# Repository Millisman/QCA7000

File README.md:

# QCA7000
QCA7000 PLC Board
1. TODO Not tested

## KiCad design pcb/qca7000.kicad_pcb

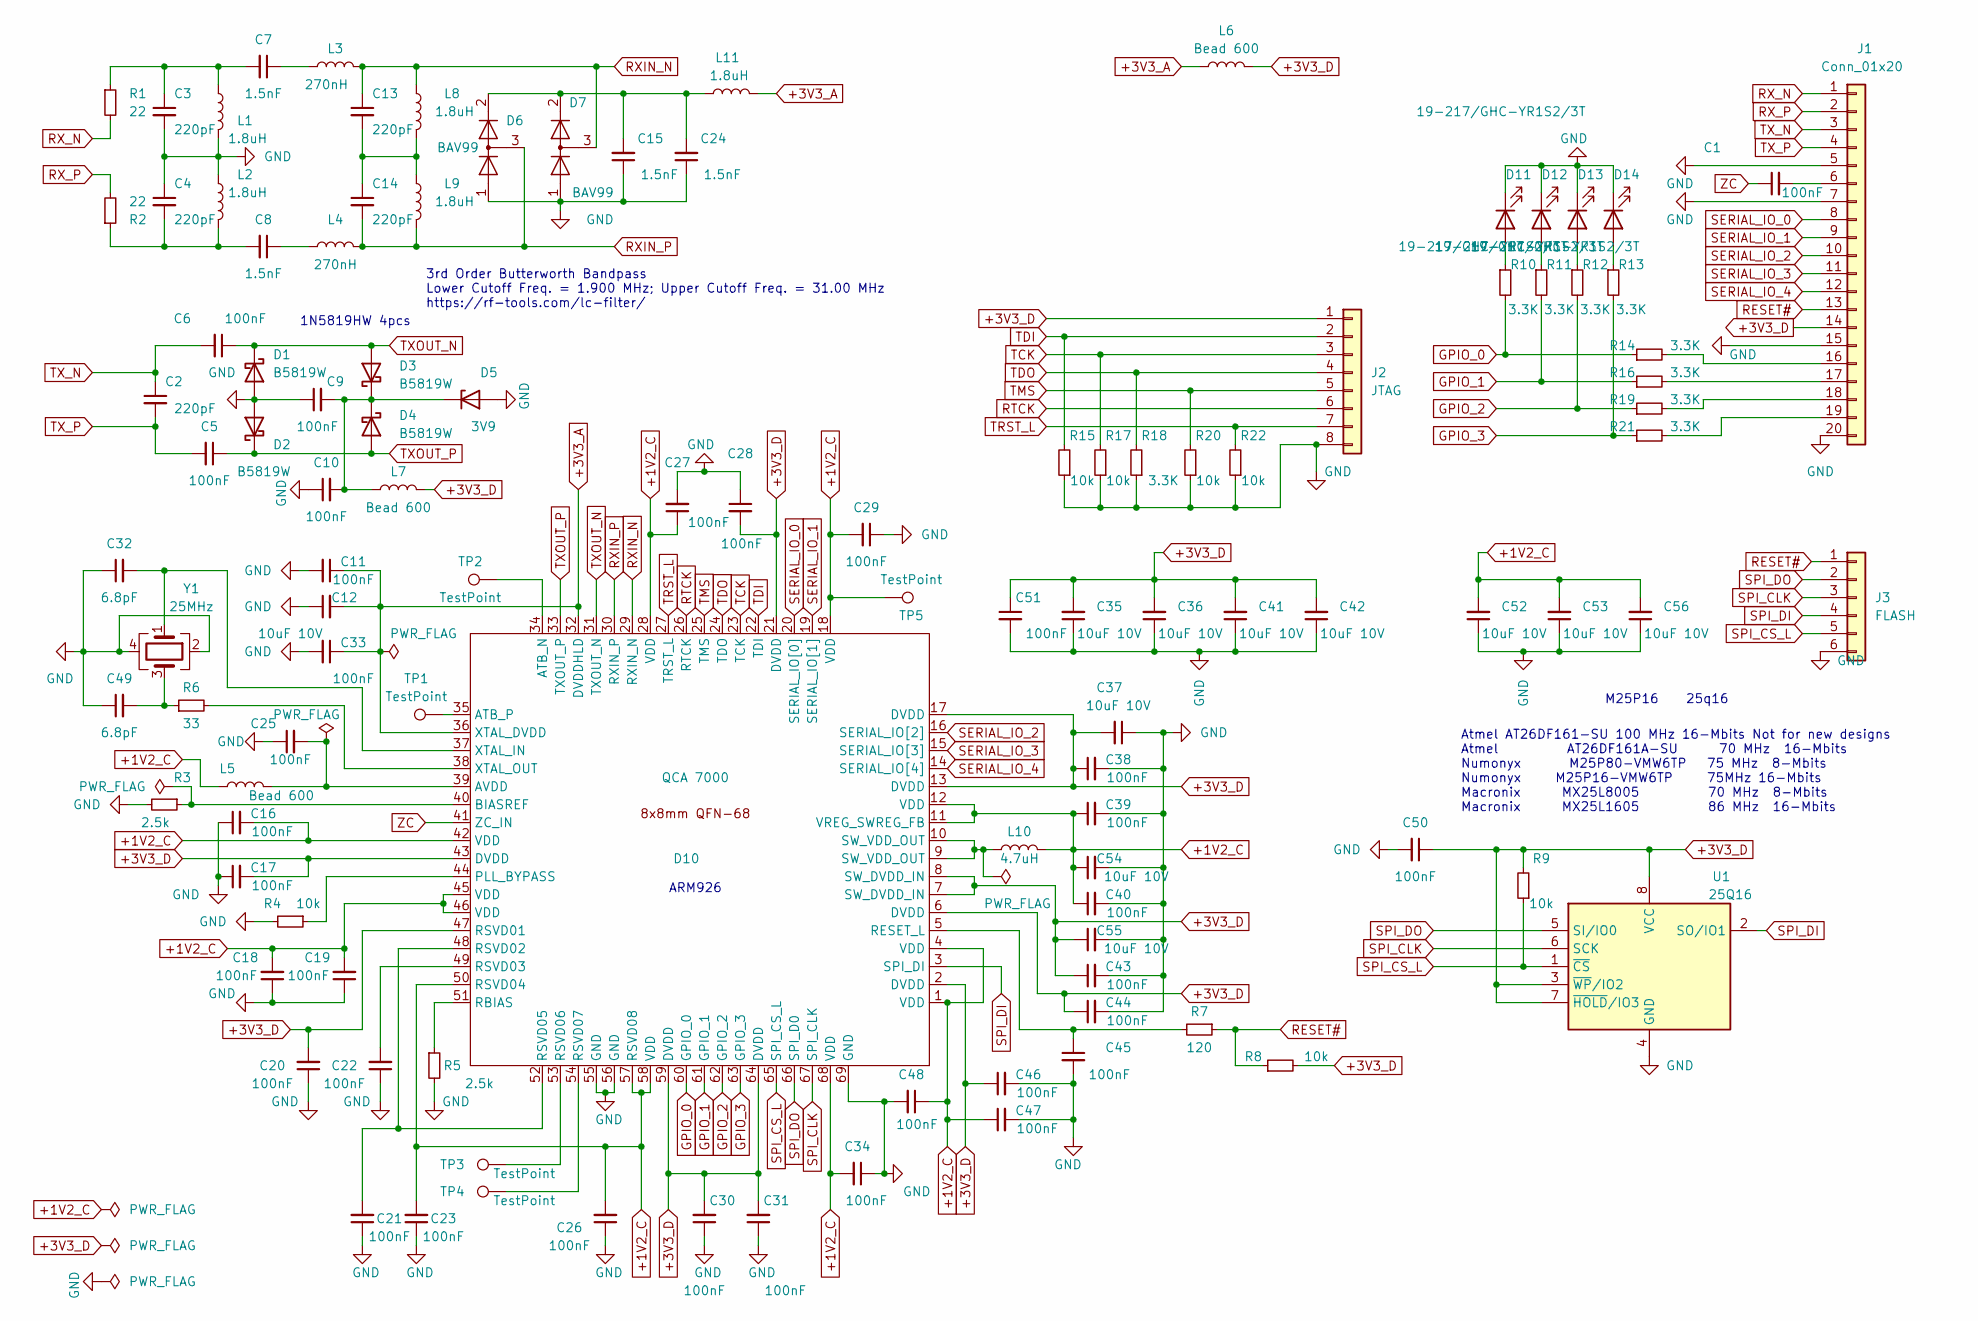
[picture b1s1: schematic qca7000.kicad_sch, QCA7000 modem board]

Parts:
C1, C5, C6, C9, C10, C11, C16, C17, C18, C19, C20, C21, C22, C23, C25, C26, C27, C28, C29, C30, C31, C33, C34, C38, C39, C40, C43, C44, C45, C46, C47, C48, C50, C51: 100nF; C_0603_1608Metric; LCSC C14663
C2, C3, C4, C13, C14: 220pF; C_0603_1608Metric; LCSC C1603
C7, C8, C15, C24: 1.5nF; C_0603_1608Metric; LCSC C1595
C12, C35, C36, C37, C41, C42, C52, C53, C54, C55, C56: 10uF 10V; C_0603_1608Metric; LCSC C19702
C32, C49: 6.8pF; C_0603_1608Metric; LCSC C1679
D1, D2, D3, D4: B5819W; D_SOD-123; LCSC C8598
D5: 3V9; D_SMA; LCSC C438352
D6, D7: BAV99; SOT-23; LCSC C2500
D10: QCA 7000; QFN-68-1EP_8x8mm_P0.4mm_EP5.2x5.2mm_ThermalVias
D11, D12, D13, D14: 19-217/GHC-YR1S2/3T; LED_0603_1608Metric; LCSC C72043
J1: Conn_01x20; PinSocket_1x20_P2.00mm_Vertical
J2: JTAG; PinHeader_1x08_P2.00mm_Vertical
J3: FLASH; PinSocket_1x06_P2.00mm_Vertical
L1, L2, L8, L9, L11: 1.8uH; L_0603_1608Metric; LCSC C78153
L3, L4: 270nH; L_0603_1608Metric; LCSC C381901
L5, L6, L7: Bead 600; L_0603_1608Metric; LCSC C1002
L10: 4.7uH; L_1206_3216Metric; LCSC C162588
R1, R2: 22; R_0603_1608Metric; LCSC C23345
R3, R5: 2.5k; R_0603_1608Metric; LCSC C304065
R4, R8, R9, R15, R17, R20, R22: 10k; R_0603_1608Metric; LCSC C25804
R6: 33; R_0603_1608Metric; LCSC C23140
R7: 120; R_0603_1608Metric; LCSC C22787
R10, R11, R12, R13, R14, R16, R18, R19, R21: 3.3K; R_0603_1608Metric; LCSC C22978
TP1, TP2, TP3, TP4, TP5: TestPoint; TestPoint_Pad_D1.0mm
U1: 25Q16; SOP-8_5.28x5.23mm_P1.27mm; LCSC C115407
Y1: 25MHz; Crystal_SMD_TXC_7M-4Pin_3.2x2.5mm; LCSC C9006

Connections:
+1V2_C: C16.2, C18.2, C19.2, C23.2, C26.2, C27.1, C29.2, C34.2, C39.1, C40.1, C47.1, C48.1, C52.2, C53.2, C54.1, C56.2, D10.1 (VDD), D10.4 (VDD), D10.11 (VREG_SWREG_FB), D10.12 (VDD), D10.18 (VDD), D10.28 (VDD), D10.42 (VDD), D10.45 (VDD), D10.46 (VDD), D10.50 (RSVD04), D10.57 (RSVD08), D10.58 (VDD), D10.68 (VDD), L5.2, L10.2, TP5.1
+3V3_A: C11.1, C12.2, C33.1, D10.32 (DVDDHLD), D10.36 (XTAL_DVDD), L6.1, L11.2
+3V3_D: C17.2, C20.2, C28.2, C30.2, C31.2, C35.2, C36.2, C37.2, C38.1, C41.2, C42.2, C43.1, C44.1, C46.1, C50.1, C51.1, C55.1, D10.2 (DVDD), D10.6 (DVDD), D10.7 (SW_DVDD_IN), D10.8 (SW_DVDD_IN), D10.13 (DVDD), D10.17 (DVDD), D10.21 (DVDD), D10.43 (DVDD), D10.47 (RSVD01), D10.59 (DVDD), D10.64 (DVDD), J1.14, J2.1, L6.2, L7.2, R8.2, R9.2, U1.3 (~WP/IO2), U1.7 (~HOLD/IO3), U1.8 (VCC)
GND: C3.2, C4.1, C9.1, C10.1, C11.2, C12.1, C15.1, C16.1, C17.1, C18.1, C19.1, C20.1, C21.1, C22.1, C23.1, C24.1, C25.1, C26.1, C27.2, C28.1, C29.1, C30.1, C31.1, C32.1, C33.2, C34.1, C35.1, C36.1, C37.1, C38.2, C39.2, C40.2, C41.1, C42.1, C43.2, C44.2, C45.2, C46.2, C47.2, C48.2, C49.1, C50.2, C51.2, C52.1, C53.1, C54.2, C55.2, C56.1, D1.2 (A), D2.2 (A), D5.2 (A), D6.1 (K), D7.1 (K), D10.55 (GND), D10.56 (GND), D10.69 (GND), D11.1 (K), D12.1 (K), D13.1 (K), D14.1 (K), J1.5, J1.7, J1.15, J1.20, J2.8, J3.6, L1.2, L2.1, R3.2, R4.2, R5.2, R15.1, R17.1, R18.1, R20.1, R22.1, U1.4 (GND), Y1.2, Y1.4
GPIO_0: D10.60 (GPIO_0), R10.2, R14.1
GPIO_1: D10.61 (GPIO_1), R11.2, R16.1
GPIO_2: D10.62 (GPIO_2), R12.2, R19.1
GPIO_3: D10.63 (GPIO_3), R13.2, R21.1
unnamed: C1.2, J1.6
unnamed: C3.1, C7.2, L1.1, R1.1
unnamed: C4.2, C8.2, L2.2, R2.1
unnamed: C7.1, L3.1
unnamed: C8.1, L4.1
unnamed: C9.2, C10.2, D3.1 (K), D4.1 (K), D5.1 (K), L7.1
unnamed: C13.2, C14.1, L8.2, L9.1
unnamed: C15.2, C24.2, D6.2 (A), D7.2 (A), L11.1
unnamed: C21.2, D10.48 (RSVD02), D10.52 (RSVD05)
unnamed: C22.2, D10.49 (RSVD03)
unnamed: C25.2, D10.39 (AVDD), L5.1
unnamed: C32.2, D10.37 (XTAL_IN), Y1.1
unnamed: C45.1, D10.5 (RESET_L), R7.2
unnamed: C49.2, R6.1, Y1.3
unnamed: D10.9 (SW_VDD_OUT), D10.10 (SW_VDD_OUT), L10.1
unnamed: D10.34 (ATB_N), TP2.1
unnamed: D10.35 (ATB_P), TP1.1
unnamed: D10.38 (XTAL_OUT), R6.2
unnamed: D10.40 (BIASREF), R3.1
unnamed: D10.44 (PLL_BYPASS), R4.1
unnamed: D10.51 (RBIAS), R5.1
unnamed: D10.53 (RSVD06), TP3.1
unnamed: D10.54 (RSVD07), TP4.1
unnamed: D11.2 (A), R10.1
unnamed: D12.2 (A), R11.1
unnamed: D13.2 (A), R12.1
unnamed: D14.2 (A), R13.1
unnamed: J1.16, R14.2
unnamed: J1.17, R16.2
unnamed: J1.18, R19.2
unnamed: J1.19, R21.2
RESET#: J1.13, J3.1, R7.1, R8.1
RTCK: D10.26 (RTCK), J2.6
RXIN_N: C13.1, D7.3 (K), D10.29 (RXIN_N), L3.2, L8.1
RXIN_P: C14.2, D6.3 (K), D10.30 (RXIN_P), L4.2, L9.2
RX_N: J1.1, R1.2
RX_P: J1.2, R2.2
SERIAL_IO_0: D10.20 (SERIAL_IO[0]), J1.8
SERIAL_IO_1: D10.19 (SERIAL_IO[1]), J1.9
SERIAL_IO_2: D10.16 (SERIAL_IO[2]), J1.10
SERIAL_IO_3: D10.15 (SERIAL_IO[3]), J1.11
SERIAL_IO_4: D10.14 (SERIAL_IO[4]), J1.12
SPI_CLK: D10.67 (SPI_CLK), J3.3, U1.6 (SCK)
SPI_CS_L: D10.65 (SPI_CS_L), J3.5, R9.1, U1.1 (~CS)
SPI_DI: D10.3 (SPI_DI), J3.4, U1.2 (SO/IO1)
SPI_DO: D10.66 (SPI_D0), J3.2, U1.5 (SI/IO0)
TCK: D10.23 (TCK), J2.3, R17.2
TDI: D10.22 (TDI), J2.2, R15.2
TDO: D10.24 (TDO), J2.4, R18.2
TMS: D10.25 (TMS), J2.5, R20.2
TRST_L: D10.27 (TRST_L), J2.7, R22.2
TXOUT_N: C6.1, D1.1 (K), D3.2 (A), D10.31 (TXOUT_N)
TXOUT_P: C5.1, D2.1 (K), D4.2 (A), D10.33 (TXOUT_P)
TX_N: C2.1, C6.2, J1.3
TX_P: C2.2, C5.2, J1.4
ZC: C1.1, D10.41 (ZC_IN)

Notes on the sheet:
1N5819HW 4pcs
Atmel AT26DF161-SU 100 MHz 16-Mbits Not for new designs Atmel AT26DF161A-SU 70 MHz 16-Mbits Numonyx M25P80-VMW6TP 75 MHz 8-Mbits Numonyx M25P16-VMW6TP 75MHz 16-Mbits Macronix MX25L8005 70 MHz 8-Mbits Macronix MX25L1605 86 MHz 16-Mbits
ARM926
3rd Order Butterworth Bandpass Lower Cutoff Freq. = 1.900 MHz; Upper Cutoff Freq. = 31.00 MHz https://rf-tools.com/lc-filter/
M25P16
25q16

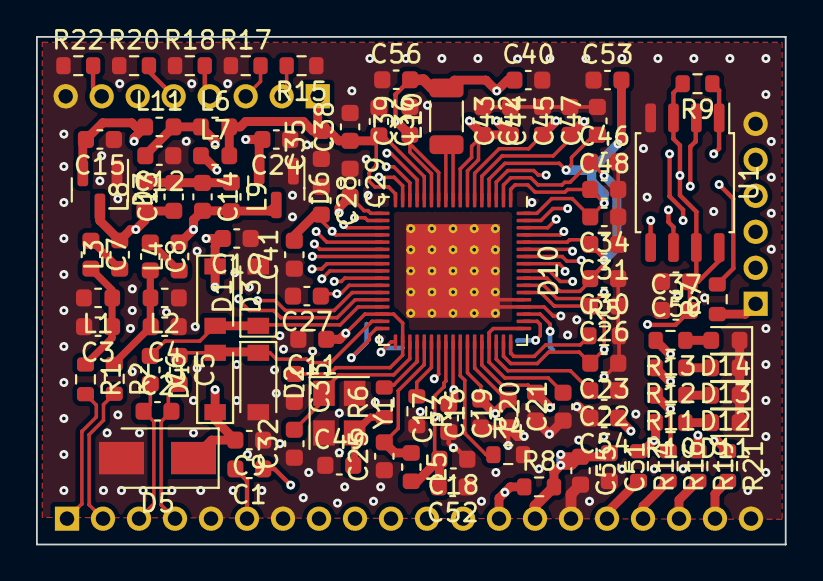
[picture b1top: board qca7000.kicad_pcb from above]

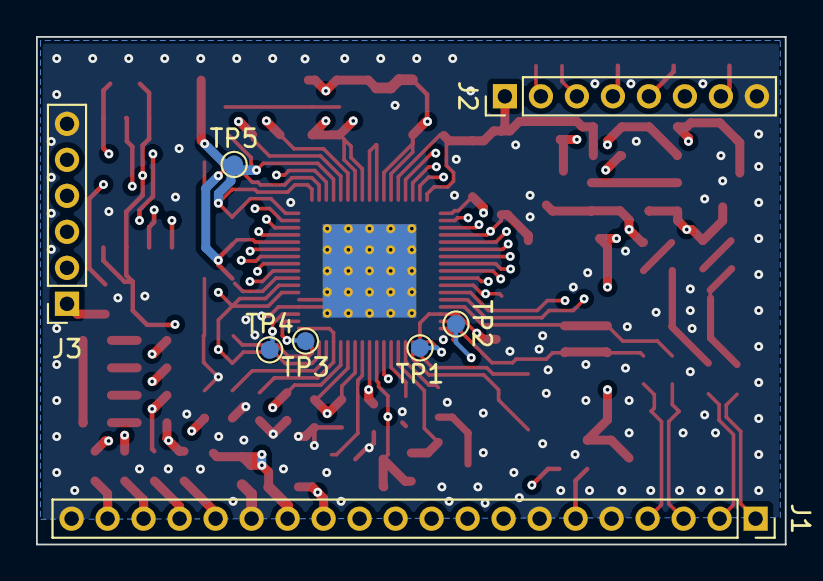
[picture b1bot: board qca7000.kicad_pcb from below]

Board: 4 copper layers, 41.6 x 28.2 mm, 111 parts (8 on the bottom side), 64 nets.

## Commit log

2022-01-03 First KiCad6 PCB
2022-01-03 added model
2022-03-03 v2, new filter, rbias
